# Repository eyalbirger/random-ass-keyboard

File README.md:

# random ass keyboard
this is my first entery into the stm32 world... im building a stm32 numpad +4keys + knob + under glow hot swap build. i will be using zmk and jlcPCBA service.

to use this you will need to program it via qmk, and solder the pcb yourself. you will also need hardware to assemble it.

BOM:

| quantity | name | value/lcsc |
|:--------:|:----:|:------|
| 21 | hot swap sockets | . |
| 1 | ec11 | . |
| 1 | push button | TL3342 |
| 1 | esd | USBLC6-2SC6 |
| 1 | fuse | Fuse_0603 |
| 5 | capacitor 0402 | 100nF |
| 3 | capacitor 0402 | 1uF |
| 2 | capacitor 0402 | 4.7uF |
| 1 | polarized capacitor | 100uF, 10v |
| 2 | resistor 0402 | 5.1k |
| 1 | resistor 0402 | 10k |
| 1 | resistor 0805 | 330R |
| 22 | diode sod | 123 |
| 12 | led | ws2812b |
| 1 | stm32 | stm32f072cbt6 |
| 1 | voltage regulator | XC6206 |
| 1 | usb c | USB_C_HRO_TYPE-C-31-M-12 |  
---
  
this should cost about 150$
  
this is the board.
you should have the pcb seperated from the plate and back.
you should assemble them with m2 screws and then put the switches in.
  
qmk firmware will be coming shortly

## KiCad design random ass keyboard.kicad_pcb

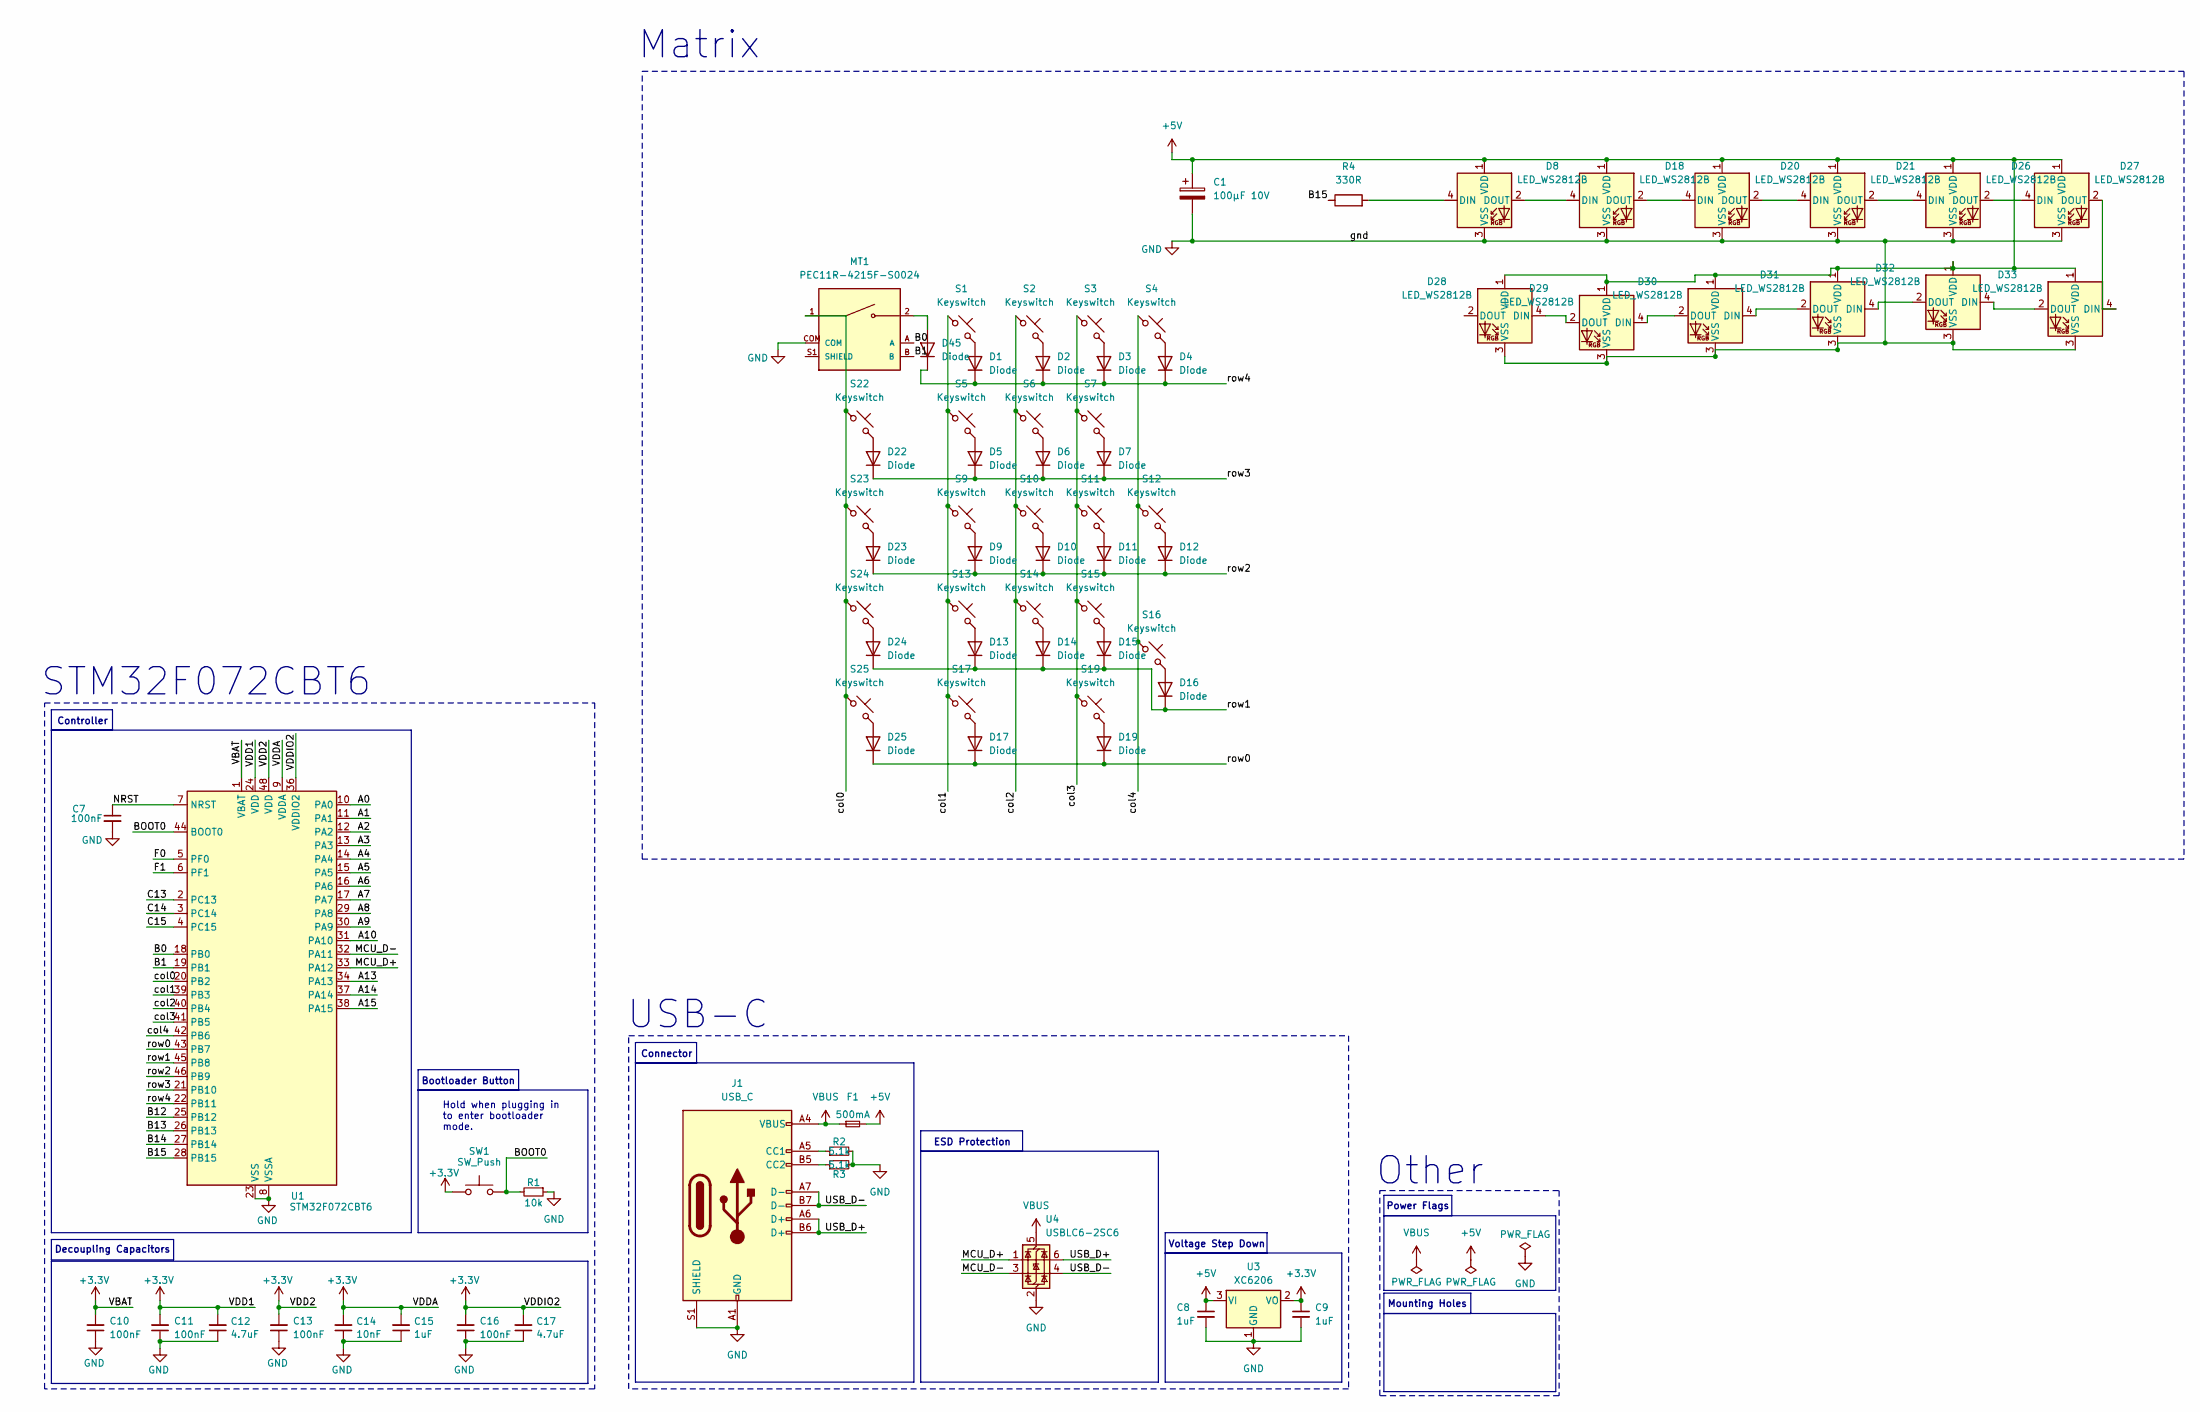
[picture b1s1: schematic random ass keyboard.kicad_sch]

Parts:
C1: 100µF 10V; CP_EIA-7343-31_Kemet-D_HandSolder; LCSC C16133
C7: 100nF; Capacitor_0402; LCSC C307331
C8, C9: 1uF; Capacitor_0402; LCSC C52923
C10, C11, C13, C16: 100nF; Capacitor_0402; MPN CL05B104KB54PNC; LCSC C307331
C12, C17: 4.7uF; Capacitor_0402; MPN CL05A475MP5NRNC; LCSC C23733
C14: 10nF; Capacitor_0402; MPN CL05B103KB5NNNC; LCSC C15195
C15: 1uF; Capacitor_0402; MPN CL05A105KA5NQNC; LCSC C52923
D1, D2, D3, D4, D5, D6, D7, D9, D10, D11, D12, D13, D14, D15, D16, D17, D19, D22, D24, D25, D45: Diode; Diode_SOD-123; LCSC C2128
D8, D18, D20, D21, D26, D27, D28, D29, D30, D31, D32, D33: LED_WS2812B; LCSC C292004
D23: Diode; Diode_SOD-123
F1: 500mA; Fuse_0603; LCSC C210357
J1: USB_C; USB_C_HRO_TYPE-C-31-M-12; LCSC C165948
MT1: PEC11R-4215F-S0024; RotaryEncoder_Alps_EC11E-Switch_Vertical_H20mm; PARTREV Rev. 09/19; LCSC PEC11R-4215F-S0024
R1: 10k; Resistor_0402; LCSC C25744
R2, R3: 5.1k; Resistor_0402; LCSC C25905
R4: 330R; Resistor_0805; LCSC C23138
S1: Keyswitch; SW_MX_HS_CPG151101S11_1u
S2, S3, S4, S5, S6, S7, S9, S10, S11, S13, S14, S15, S19, S22, S23, S24, S25: Keyswitch; SW_MX_HS_CPG151101S11_1u; LCSC CPG151101S11-16
S12, S16, S17: Keyswitch; SW_MX_HS_CPG151101S11_1.5u; LCSC CPG151101S11-16
SW1: SW_Push; Button_TL3342; LCSC C115351
U1: STM32F072CBT6; Package_LQFP-48_7x7mm_P0.5; LCSC C81720
U3: XC6206; Voltage_SOT-23; LCSC C5446
U4: USBLC6-2SC6; ESD_SOT-23-6; LCSC C2827654

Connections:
+3.3V: C9.1, C10.2, C11.2, C12.2, C13.2, C14.2, C15.2, C16.2, C17.2, SW1.1, U1.1 (VBAT), U1.9 (VDDA), U1.24 (VDD), U1.36 (VDDIO2), U1.48 (VDD), U3.2 (VO)
+5V: C1.1, C8.1, D8.1 (VDD), D18.1 (VDD), D20.1 (VDD), D21.1 (VDD), D26.1 (VDD), D27.1 (VDD), D28.1 (VDD), D29.1 (VDD), D30.1 (VDD), D31.1 (VDD), D32.1 (VDD), D33.1 (VDD), F1.2, U3.3 (VI)
/A0: U1.10 (PA0)
/A1: U1.11 (PA1)
/A2: U1.12 (PA2)
/A3: U1.13 (PA3)
/A4: U1.14 (PA4)
/A5: U1.15 (PA5)
/A6: U1.16 (PA6)
/A7: U1.17 (PA7)
/A8: U1.29 (PA8)
/A9: U1.30 (PA9)
/A10: U1.31 (PA10)
/A13: U1.34 (PA13)
/A14: U1.37 (PA14)
/A15: U1.38 (PA15)
/B0: MT1.A, U1.18 (PB0)
/B1: MT1.B, U1.19 (PB1)
/B12: U1.25 (PB12)
/B13: U1.26 (PB13)
/B14: U1.27 (PB14)
/B15: R4.1, U1.28 (PB15)
/BOOT0: R1.2, SW1.2, U1.44 (BOOT0)
/C13: U1.2 (PC13)
/C14: U1.3 (PC14)
/C15: U1.4 (PC15)
/F0: U1.5 (PF0)
/F1: U1.6 (PF1)
/MCU_D+: U1.33 (PA12), U4.1 (I/O1)
/MCU_D-: U1.32 (PA11), U4.3 (I/O2)
/NRST: C7.1, U1.7 (NRST)
/USB_D+: J1.A6 (D+), J1.B6 (D+), U4.6 (I/O1)
/USB_D-: J1.A7 (D-), J1.B7 (D-), U4.4 (I/O2)
/col0: MT1.1, S22.1, S23.1, S24.1, S25.1, U1.20 (PB2)
/col1: S1.1, S5.1, S9.1, S13.1, S17.1, U1.39 (PB3)
/col2: S2.1, S6.1, S10.1, S14.1, U1.40 (PB4)
/col3: S3.1, S7.1, S11.1, S15.1, S19.1, U1.41 (PB5)
/col4: S4.1, S12.1, S16.1, U1.42 (PB6)
/row0: D17.1 (K), D19.1 (K), D25.1 (K), U1.43 (PB7)
/row1: D13.1 (K), D14.1 (K), D15.1 (K), D16.1 (K), D24.1 (K), U1.45 (PB8)
/row2: D9.1 (K), D10.1 (K), D11.1 (K), D12.1 (K), D23.1 (K), U1.46 (PB9)
/row3: D5.1 (K), D6.1 (K), D7.1 (K), D22.1 (K), U1.21 (PB10)
/row4: D1.1 (K), D2.1 (K), D3.1 (K), D4.1 (K), D45.1 (K), U1.22 (PB11)
GND: C1.2, C7.2, C8.2, C9.2, C10.1, C11.1, C12.1, C13.1, C14.1, C15.1, C16.1, C17.1, D8.3 (VSS), D18.3 (VSS), D20.3 (VSS), D21.3 (VSS), D26.3 (VSS), D27.3 (VSS), D28.3 (VSS), D29.3 (VSS), D30.3 (VSS), D31.3 (VSS), D32.3 (VSS), D33.3 (VSS), J1.A1 (GND), J1.A12 (GND), J1.B1 (GND), J1.B12 (GND), J1.S1 (SHIELD), MT1.COM, R1.1, R2.2, R3.2, U1.8 (VSSA), U1.23 (VSS), U1.35 (VSS), U1.47 (VSS), U3.1 (GND), U4.2 (GND)
unnamed: D1.2 (A), S1.2
unnamed: D2.2 (A), S2.2
unnamed: D3.2 (A), S3.2
unnamed: D4.2 (A), S4.2
unnamed: D5.2 (A), S5.2
unnamed: D6.2 (A), S6.2
unnamed: D7.2 (A), S7.2
unnamed: D8.4 (DIN), R4.2
unnamed: D9.2 (A), S9.2
unnamed: D10.2 (A), S10.2
unnamed: D11.2 (A), S11.2
unnamed: D12.2 (A), S12.2
unnamed: D13.2 (A), S13.2
unnamed: D14.2 (A), S14.2
unnamed: D15.2 (A), S15.2
unnamed: D16.2 (A), S16.2
unnamed: D17.2 (A), S17.2
unnamed: D8.2 (DOUT), D18.4 (DIN)
unnamed: D18.2 (DOUT), D20.4 (DIN)
unnamed: D19.2 (A), S19.2
unnamed: D20.2 (DOUT), D21.4 (DIN)
unnamed: D21.2 (DOUT), D26.4 (DIN)
unnamed: D22.2 (A), S22.2
unnamed: D23.2 (A), S23.2
unnamed: D24.2 (A), S24.2
unnamed: D25.2 (A), S25.2
unnamed: D26.2 (DOUT), D27.4 (DIN)
unnamed: D27.2 (DOUT), D33.4 (DIN)
unnamed: D28.4 (DIN), D29.2 (DOUT)
unnamed: D29.4 (DIN), D30.2 (DOUT)
unnamed: D30.4 (DIN), D31.2 (DOUT)
unnamed: D31.4 (DIN), D32.2 (DOUT)
unnamed: D32.4 (DIN), D33.2 (DOUT)
unnamed: D45.2 (A), MT1.2
unnamed: J1.A5 (CC1), R2.1
unnamed: J1.B5 (CC2), R3.1
unnamed: MT1.S1 (SHIELD), MT1.S2 (SHIELD)
VBUS: F1.1, J1.A4 (VBUS), J1.A9 (VBUS), J1.B4 (VBUS), J1.B9 (VBUS), U4.5 (VBUS)

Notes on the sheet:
STM32F072CBT6
USB-C
Mounting Holes
Decoupling Capacitors
Controller
ESD Protection
Power Flags
Voltage Step Down
Other
Bootloader Button
Matrix
Connector
Hold when plugging in to enter bootloader mode.

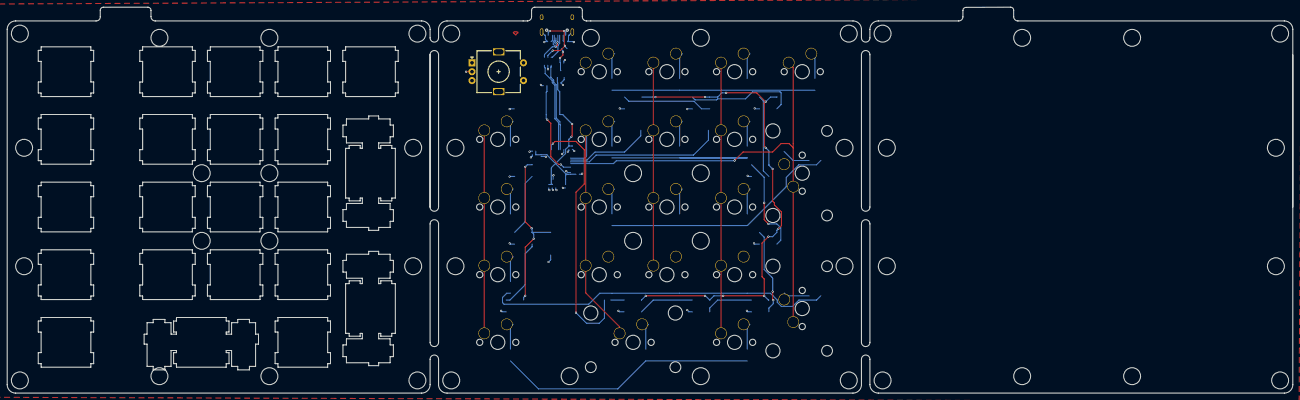
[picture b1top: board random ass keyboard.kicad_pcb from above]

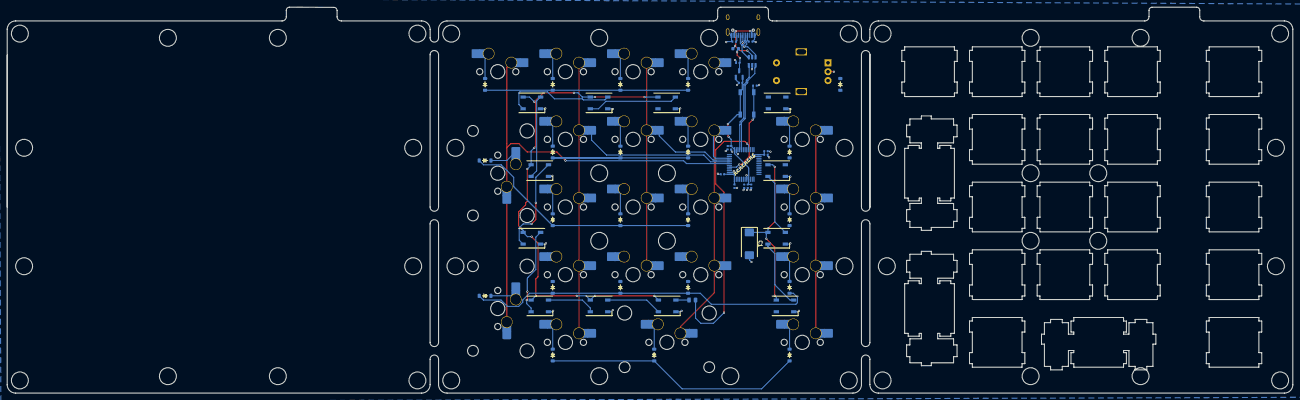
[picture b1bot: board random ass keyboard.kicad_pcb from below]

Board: 4 copper layers, 361.9 x 108.6 mm, 78 parts (77 on the bottom side), 59 nets.

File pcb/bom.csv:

Designator,Footprint,Quantity,Value,LCSC Part #
C1,CP_EIA-7343-31_Kemet-D_HandSolder,1,100µF 10V,C16133
"C10, C11, C13, C16, C7",Capacitor_0402,5,100nF,C307331
"C12, C17",Capacitor_0402,2,4.7uF,C23733
C14,Capacitor_0402,1,10nF,C15195
"C15, C8, C9",Capacitor_0402,3,1uF,C52923
"D1, D10, D11, D12, D13, D14, D15, D16, D17, D19, D2, D22, D23, D24, D25, D3, D34, D4, D5, D6, D7, D9",Diode_SOD-123,22,Diode,C2128
"D18, D20, D21, D26, D27, D28, D29, D30, D31, D32, D33, D8",LED_WS2812B,12,LED_WS2812B,C292004
F1,Fuse_0603,1,500mA,C210357
J1,USB_C_HRO_TYPE-C-31-M-12,1,USB_C,C165948
R1,Resistor_0402,1,10k,C25744
"R2, R3",Resistor_0402,2,5.1k,C25905
R4,Resistor_0805,1,330R,C23138
S1,SW_MX_HS_CPG151101S11_1u,1,Keyswitch,
"S10, S11, S13, S14, S15, S19, S2, S22, S23, S24, S25, S3, S4, S5, S6, S7, S9",SW_MX_HS_CPG151101S11_1u,17,Keyswitch,CPG151101S11-16
"S12, S16, S17",SW_MX_HS_CPG151101S11_1.5u,3,Keyswitch,CPG151101S11-16
SW1,Button_TL3342,1,SW_Push,C115351
SW2,RotaryEncoder_Alps_EC11E-Switch_Vertical_H20mm_MountingHoles,1,RotaryEncoder_Switch,
U1,Package_LQFP-48_7x7mm_P0.5,1,STM32F072CBT6,C81720
U3,Voltage_SOT-23,1,XC6206,C5446
U4,ESD_SOT-23-6,1,USBLC6-2SC6,C2827654

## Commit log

2026-03-17 schem
2026-03-17 i... actually finished this shit.
2026-03-17 fab files but also i need to add silk screen
2026-03-18 bom and fab
2026-03-18 other things
2026-03-25 fixed screw hole and knob hole
2026-03-26 bom, readme, garber and pcb art
2026-03-26 updated that one diode
2026-03-26 upgraded to kicad ten and it gave me so much problemssss
2026-03-27 finalll shit
2026-03-28 changed the plate
2026-03-28 change the plate
2026-03-29 broski
2026-05-02 pcb and organized
